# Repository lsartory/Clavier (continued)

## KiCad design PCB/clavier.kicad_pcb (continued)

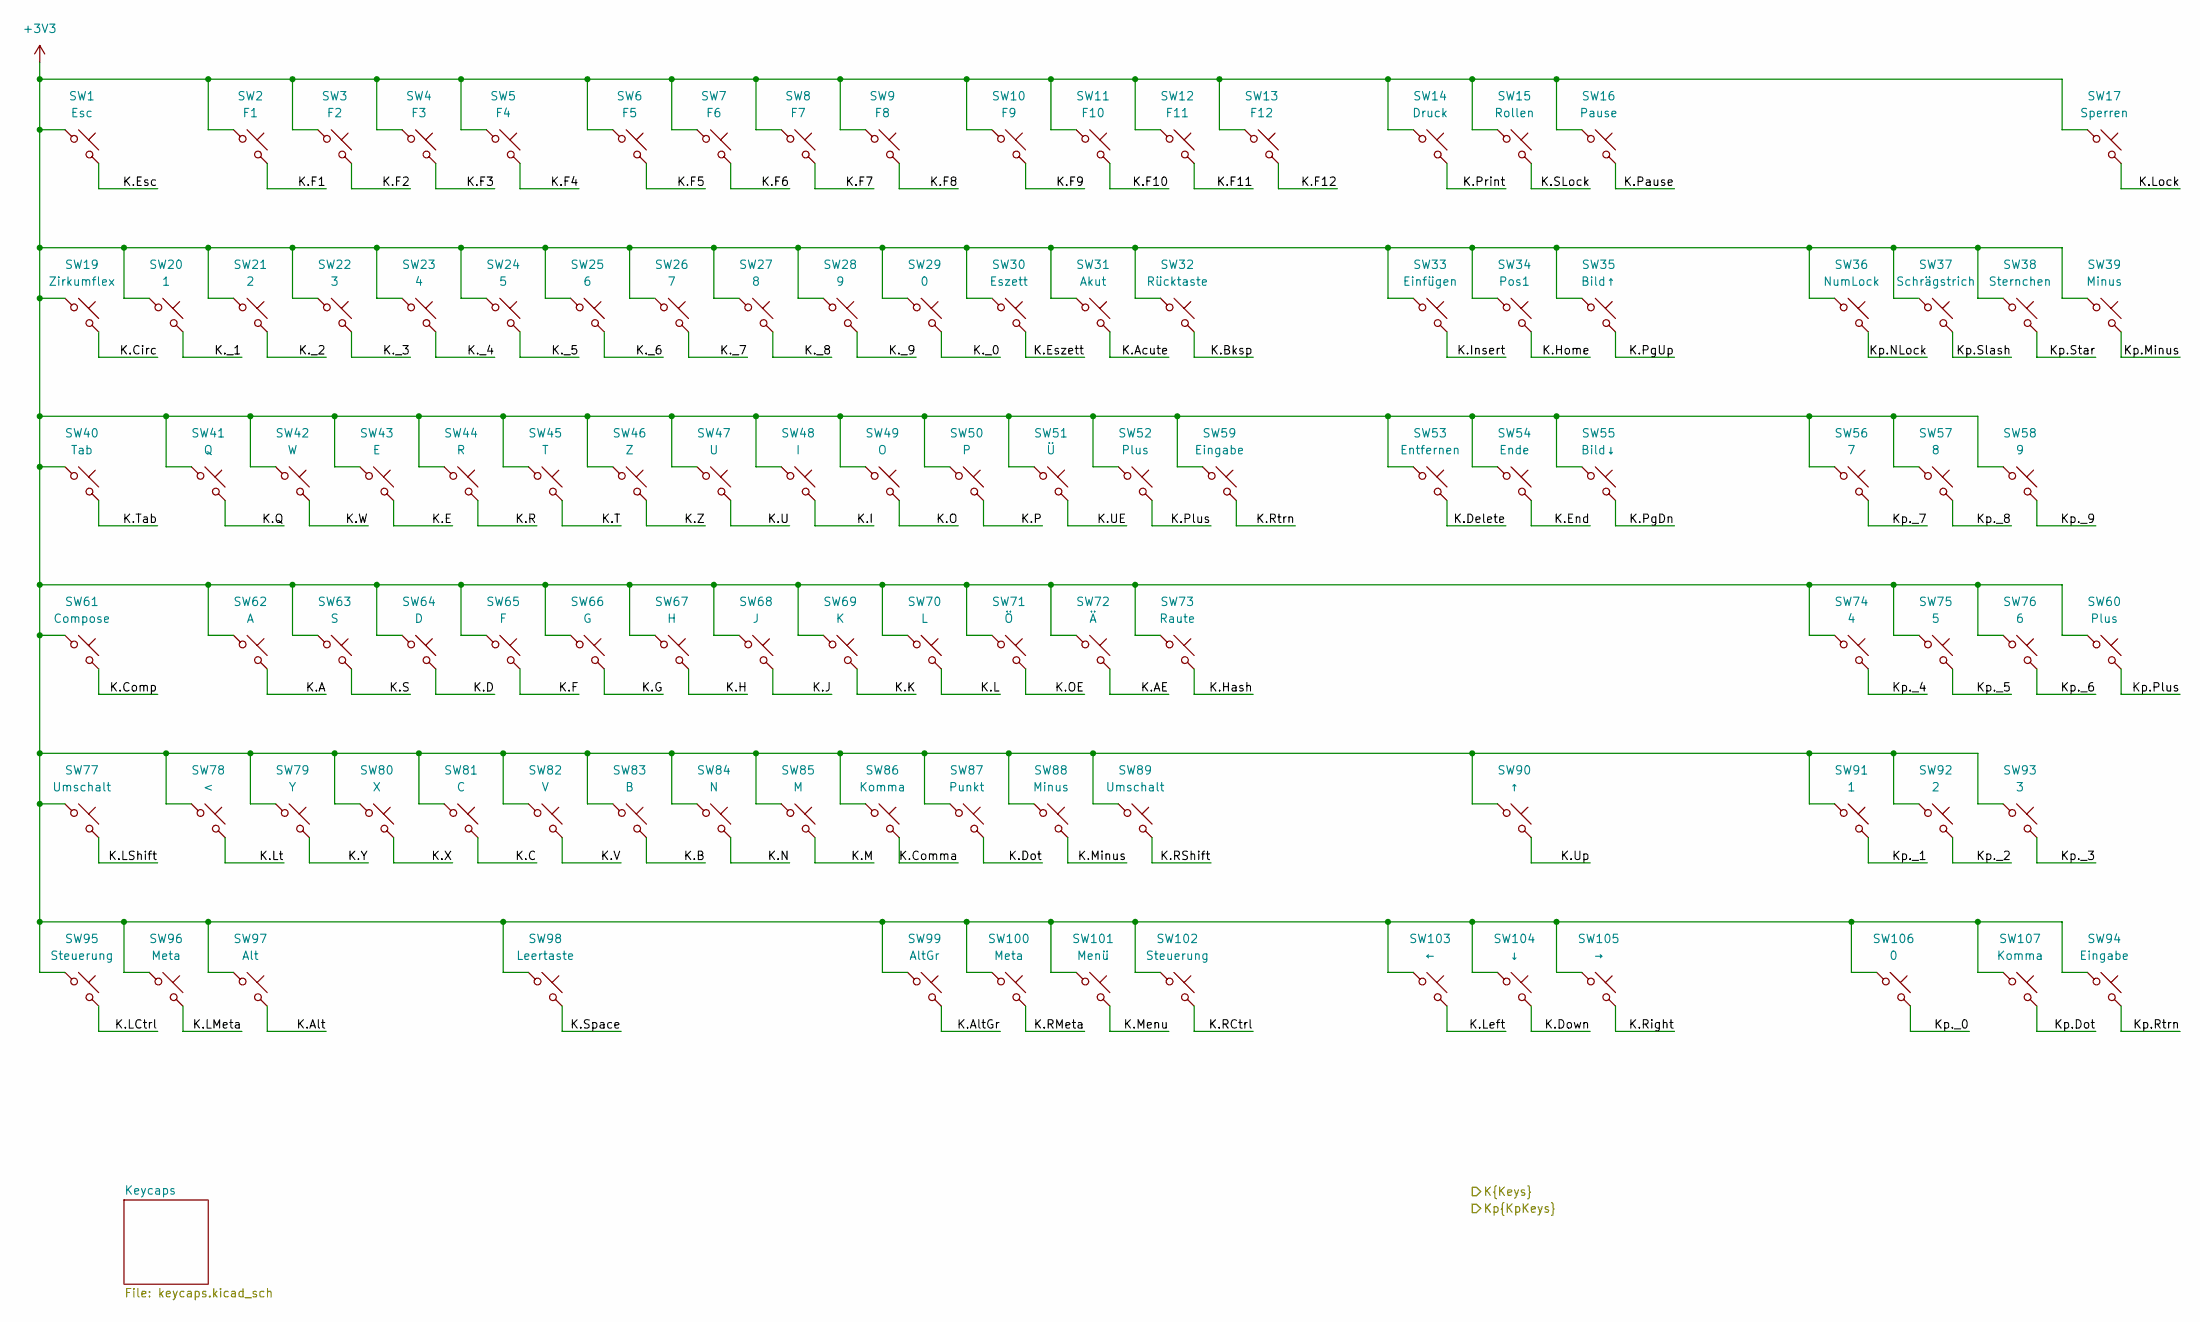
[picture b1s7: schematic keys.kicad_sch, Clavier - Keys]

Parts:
SW1, SW2, SW3, SW4, SW5, SW6, SW7, SW8, SW9, SW10, SW11, SW12, SW13, SW14, SW15, SW16, SW17, SW19, SW20, SW21, SW22, SW23, SW24, SW25, SW26, SW27, SW28, SW29, SW30, SW31, SW33, SW34, SW35, SW36, SW37, SW38, SW39, SW41, SW42, SW43, SW44, SW45, SW46, SW47, SW48, SW49, SW50, SW51, SW52, SW53, SW54, SW55, SW56, SW57, SW58, SW62, SW63, SW64, SW65, SW66, SW67, SW68, SW69, SW70, SW71, SW72, SW73, SW74, SW75, SW76, SW78, SW79, SW80, SW81, SW82, SW83, SW84, SW85, SW86, SW87, SW88, SW90, SW91, SW92, SW93, SW103, SW104, SW105, SW107: SW_Cherry_MX_1.00u_PCB
SW32, SW106: SW_Cherry_MX_2.00u_PCB
SW40: SW_Cherry_MX_1.50u_PCB
SW59: SW_Cherry_MX_ISOEnter_PCB
SW60, SW94: SW_Cherry_MX_2.00u_Vertical_PCB
SW61: SW_Cherry_MX_1.75u_PCB
SW77, SW95, SW96, SW97, SW99, SW100, SW101, SW102: SW_Cherry_MX_1.25u_PCB
SW89: SW_Cherry_MX_2.75u_PCB
SW98: SW_Cherry_MX_6.25u_PCB

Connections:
+3V3: SW1.1, SW2.1, SW3.1, SW4.1, SW5.1, SW6.1, SW7.1, SW8.1, SW9.1, SW10.1, SW11.1, SW12.1, SW13.1, SW14.1, SW15.1, SW16.1, SW17.1, SW19.1, SW20.1, SW21.1, SW22.1, SW23.1, SW24.1, SW25.1, SW26.1, SW27.1, SW28.1, SW29.1, SW30.1, SW31.1, SW32.1, SW33.1, SW34.1, SW35.1, SW36.1, SW37.1, SW38.1, SW39.1, SW40.1, SW41.1, SW42.1, SW43.1, SW44.1, SW45.1, SW46.1, SW47.1, SW48.1, SW49.1, SW50.1, SW51.1, SW52.1, SW53.1, SW54.1, SW55.1, SW56.1, SW57.1, SW58.1, SW59.1, SW60.1, SW61.1, SW62.1, SW63.1, SW64.1, SW65.1, SW66.1, SW67.1, SW68.1, SW69.1, SW70.1, SW71.1, SW72.1, SW73.1, SW74.1, SW75.1, SW76.1, SW77.1, SW78.1, SW79.1, SW80.1, SW81.1, SW82.1, SW83.1, SW84.1, SW85.1, SW86.1, SW87.1, SW88.1, SW89.1, SW90.1, SW91.1, SW92.1, SW93.1, SW94.1, SW95.1, SW96.1, SW97.1, SW98.1, SW99.1, SW100.1, SW101.1, SW102.1, SW103.1, SW104.1, SW105.1, SW106.1, SW107.1; also elsewhere on the board
/FPGA/K.A: SW62.2; also elsewhere on the board
/FPGA/K.AE: SW72.2; also elsewhere on the board
/FPGA/K.Acute: SW31.2; also elsewhere on the board
/FPGA/K.Alt: SW97.2; also elsewhere on the board
/FPGA/K.AltGr: SW99.2; also elsewhere on the board
/FPGA/K.B: SW83.2; also elsewhere on the board
/FPGA/K.Bksp: SW32.2; also elsewhere on the board
/FPGA/K.C: SW81.2; also elsewhere on the board
/FPGA/K.Circ: SW19.2; also elsewhere on the board
/FPGA/K.Comma: SW86.2; also elsewhere on the board
/FPGA/K.Comp: SW61.2; also elsewhere on the board
/FPGA/K.D: SW64.2; also elsewhere on the board
/FPGA/K.Delete: SW53.2; also elsewhere on the board
/FPGA/K.Dot: SW87.2; also elsewhere on the board
/FPGA/K.Down: SW104.2; also elsewhere on the board
/FPGA/K.E: SW43.2; also elsewhere on the board
/FPGA/K.End: SW54.2; also elsewhere on the board
/FPGA/K.Esc: SW1.2; also elsewhere on the board
/FPGA/K.Eszett: SW30.2; also elsewhere on the board
/FPGA/K.F: SW65.2; also elsewhere on the board
/FPGA/K.F1: SW2.2; also elsewhere on the board
/FPGA/K.F2: SW3.2; also elsewhere on the board
/FPGA/K.F3: SW4.2; also elsewhere on the board
/FPGA/K.F4: SW5.2; also elsewhere on the board
/FPGA/K.F5: SW6.2; also elsewhere on the board
/FPGA/K.F6: SW7.2; also elsewhere on the board
/FPGA/K.F7: SW8.2; also elsewhere on the board
/FPGA/K.F8: SW9.2; also elsewhere on the board
/FPGA/K.F9: SW10.2; also elsewhere on the board
/FPGA/K.F10: SW11.2; also elsewhere on the board
/FPGA/K.F11: SW12.2; also elsewhere on the board
/FPGA/K.F12: SW13.2; also elsewhere on the board
/FPGA/K.G: SW66.2; also elsewhere on the board
/FPGA/K.H: SW67.2; also elsewhere on the board
/FPGA/K.Hash: SW73.2; also elsewhere on the board
/FPGA/K.Home: SW34.2; also elsewhere on the board
/FPGA/K.I: SW48.2; also elsewhere on the board
/FPGA/K.Insert: SW33.2; also elsewhere on the board
/FPGA/K.J: SW68.2; also elsewhere on the board
/FPGA/K.K: SW69.2; also elsewhere on the board
/FPGA/K.L: SW70.2; also elsewhere on the board
/FPGA/K.LCtrl: SW95.2; also elsewhere on the board
/FPGA/K.LMeta: SW96.2; also elsewhere on the board
/FPGA/K.LShift: SW77.2; also elsewhere on the board
/FPGA/K.Left: SW103.2; also elsewhere on the board
/FPGA/K.Lock: SW17.2; also elsewhere on the board
/FPGA/K.Lt: SW78.2; also elsewhere on the board
/FPGA/K.M: SW85.2; also elsewhere on the board
/FPGA/K.Menu: SW101.2; also elsewhere on the board
/FPGA/K.Minus: SW88.2; also elsewhere on the board
/FPGA/K.N: SW84.2; also elsewhere on the board
/FPGA/K.O: SW49.2; also elsewhere on the board
/FPGA/K.OE: SW71.2; also elsewhere on the board
/FPGA/K.P: SW50.2; also elsewhere on the board
/FPGA/K.Pause: SW16.2; also elsewhere on the board
/FPGA/K.PgDn: SW55.2; also elsewhere on the board
/FPGA/K.PgUp: SW35.2; also elsewhere on the board
/FPGA/K.Plus: SW52.2; also elsewhere on the board
/FPGA/K.Print: SW14.2; also elsewhere on the board
/FPGA/K.Q: SW41.2; also elsewhere on the board
/FPGA/K.R: SW44.2; also elsewhere on the board
/FPGA/K.RCtrl: SW102.2; also elsewhere on the board
/FPGA/K.RMeta: SW100.2; also elsewhere on the board
/FPGA/K.RShift: SW89.2; also elsewhere on the board
/FPGA/K.Right: SW105.2; also elsewhere on the board
/FPGA/K.Rtrn: SW59.2; also elsewhere on the board
/FPGA/K.S: SW63.2; also elsewhere on the board
/FPGA/K.SLock: SW15.2; also elsewhere on the board
/FPGA/K.Space: SW98.2; also elsewhere on the board
/FPGA/K.T: SW45.2; also elsewhere on the board
/FPGA/K.Tab: SW40.2; also elsewhere on the board
/FPGA/K.U: SW47.2; also elsewhere on the board
/FPGA/K.UE: SW51.2; also elsewhere on the board
/FPGA/K.Up: SW90.2; also elsewhere on the board
/FPGA/K.V: SW82.2; also elsewhere on the board
/FPGA/K.W: SW42.2; also elsewhere on the board
/FPGA/K.X: SW80.2; also elsewhere on the board
/FPGA/K.Y: SW79.2; also elsewhere on the board
/FPGA/K.Z: SW46.2; also elsewhere on the board
/FPGA/K._0: SW29.2; also elsewhere on the board
/FPGA/K._1: SW20.2; also elsewhere on the board
/FPGA/K._2: SW21.2; also elsewhere on the board
/FPGA/K._3: SW22.2; also elsewhere on the board
/FPGA/K._4: SW23.2; also elsewhere on the board
/FPGA/K._5: SW24.2; also elsewhere on the board
/FPGA/K._6: SW25.2; also elsewhere on the board
/FPGA/K._7: SW26.2; also elsewhere on the board
/FPGA/K._8: SW27.2; also elsewhere on the board
/FPGA/K._9: SW28.2; also elsewhere on the board
/FPGA/Kp.Dot: SW107.2; also elsewhere on the board
/FPGA/Kp.Minus: SW39.2; also elsewhere on the board
/FPGA/Kp.NLock: SW36.2; also elsewhere on the board
/FPGA/Kp.Plus: SW60.2; also elsewhere on the board
/FPGA/Kp.Rtrn: SW94.2; also elsewhere on the board
/FPGA/Kp.Slash: SW37.2; also elsewhere on the board
/FPGA/Kp.Star: SW38.2; also elsewhere on the board
/FPGA/Kp._0: SW106.2; also elsewhere on the board
/FPGA/Kp._1: SW91.2; also elsewhere on the board
/FPGA/Kp._2: SW92.2; also elsewhere on the board
/FPGA/Kp._3: SW93.2; also elsewhere on the board
/FPGA/Kp._4: SW74.2; also elsewhere on the board
/FPGA/Kp._5: SW75.2; also elsewhere on the board
/FPGA/Kp._6: SW76.2; also elsewhere on the board
/FPGA/Kp._7: SW56.2; also elsewhere on the board
/FPGA/Kp._8: SW57.2; also elsewhere on the board
/FPGA/Kp._9: SW58.2; also elsewhere on the board

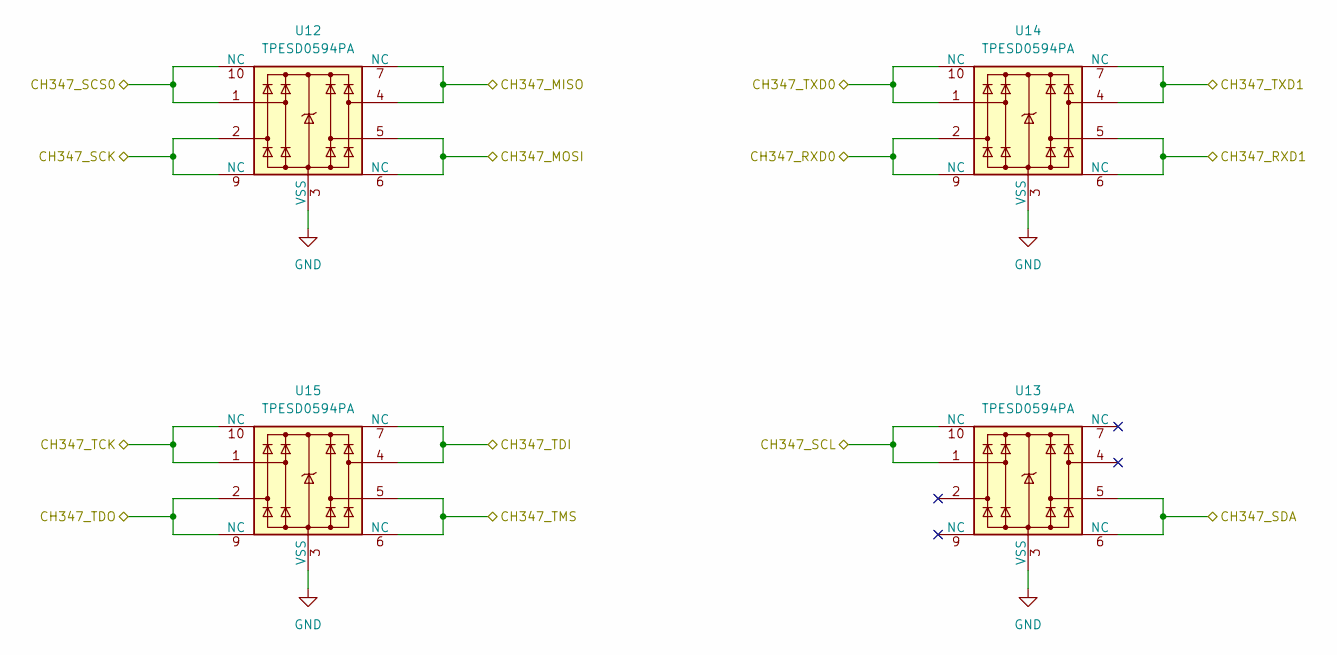
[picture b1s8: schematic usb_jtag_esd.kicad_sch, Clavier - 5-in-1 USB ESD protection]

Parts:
U12, U13, U14, U15: TPESD0594PA; Diodes_UDFN-10_1.0x2.5mm_P0.5mm; Part_number TPESD0594PA; LCSC C42436622

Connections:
/5-in-1 USB/CH347_MISO: U12.4, U12.7 (NC); also elsewhere on the board
/5-in-1 USB/CH347_MOSI: U12.5, U12.6 (NC); also elsewhere on the board
/5-in-1 USB/CH347_RXD0: U14.2, U14.9 (NC); also elsewhere on the board
/5-in-1 USB/CH347_RXD1: U14.5, U14.6 (NC); also elsewhere on the board
/5-in-1 USB/CH347_SCK: U12.2, U12.9 (NC); also elsewhere on the board
/5-in-1 USB/CH347_SCL: U13.1, U13.10 (NC); also elsewhere on the board
/5-in-1 USB/CH347_SCS0: U12.1, U12.10 (NC); also elsewhere on the board
/5-in-1 USB/CH347_SDA: U13.5, U13.6 (NC); also elsewhere on the board
/5-in-1 USB/CH347_TCK: U15.1, U15.10 (NC); also elsewhere on the board
/5-in-1 USB/CH347_TDI: U15.4, U15.7 (NC); also elsewhere on the board
/5-in-1 USB/CH347_TDO: U15.2, U15.9 (NC); also elsewhere on the board
/5-in-1 USB/CH347_TMS: U15.5, U15.6 (NC); also elsewhere on the board
/5-in-1 USB/CH347_TXD0: U14.1, U14.10 (NC); also elsewhere on the board
/5-in-1 USB/CH347_TXD1: U14.4, U14.7 (NC); also elsewhere on the board
GND: U12.3 (VSS), U12.8 (VSS), U13.3 (VSS), U13.8 (VSS), U14.3 (VSS), U14.8 (VSS), U15.3 (VSS), U15.8 (VSS); also elsewhere on the board

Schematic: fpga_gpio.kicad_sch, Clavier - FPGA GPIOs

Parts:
J5, J6: Pin header, 2x4; PinHeader_2x04_P2.54mm_Vertical; Part_number ZX-PZ2.54-2-4PZZ; LCSC C7501275
U2, U3, U9, U10: TPESD0594PA; Diodes_UDFN-10_1.0x2.5mm_P0.5mm; Part_number TPESD0594PA; LCSC C42436622

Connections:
/FPGA/FPGA_GPIO0: J5.1, U3.2, U3.9 (NC); also elsewhere on the board
/FPGA/FPGA_GPIO1: J5.3, U3.1, U3.10 (NC); also elsewhere on the board
/FPGA/FPGA_GPIO2: J5.5, U10.1, U10.10 (NC); also elsewhere on the board
/FPGA/FPGA_GPIO3: J5.7, U10.2, U10.9 (NC); also elsewhere on the board
/FPGA/FPGA_GPIO4: J5.2, U3.4, U3.7 (NC); also elsewhere on the board
/FPGA/FPGA_GPIO5: J5.4, U3.5, U3.6 (NC); also elsewhere on the board
/FPGA/FPGA_GPIO6: J5.6, U10.5, U10.6 (NC); also elsewhere on the board
/FPGA/FPGA_GPIO7: J5.8, U10.4, U10.7 (NC); also elsewhere on the board
/FPGA/FPGA_GPIO8: J6.1, U2.2, U2.9 (NC); also elsewhere on the board
/FPGA/FPGA_GPIO9: J6.3, U2.1, U2.10 (NC); also elsewhere on the board
/FPGA/FPGA_GPIO10: J6.5, U9.1, U9.10 (NC); also elsewhere on the board
/FPGA/FPGA_GPIO11: J6.7, U9.2, U9.9 (NC); also elsewhere on the board
/FPGA/FPGA_GPIO12: J6.2, U2.4, U2.7 (NC); also elsewhere on the board
/FPGA/FPGA_GPIO13: J6.4, U2.5, U2.6 (NC); also elsewhere on the board
/FPGA/FPGA_GPIO14: J6.6, U9.5, U9.6 (NC); also elsewhere on the board
/FPGA/FPGA_GPIO15: J6.8, U9.4, U9.7 (NC); also elsewhere on the board
GND: U2.3 (VSS), U2.8 (VSS), U3.3 (VSS), U3.8 (VSS), U9.3 (VSS), U9.8 (VSS), U10.3 (VSS), U10.8 (VSS); also elsewhere on the board

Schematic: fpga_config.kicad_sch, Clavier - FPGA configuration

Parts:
C30: 100nF; C_0402_1005Metric_Pad0.74x0.62mm_HandSolder; Voltage 50V; Part_number GRM155R71H104KE14D; LCSC C77020
C31, C40: 1µF; C_0402_1005Metric_Pad0.74x0.62mm_HandSolder; Voltage 50V; Part_number GRM155R61H105KE05D; LCSC C1518208
J8: Pin header, 1x4; PinHeader_1x04_P2.54mm_Horizontal; Part_number ZX-PZ2.54-1-4PWZ; LCSC C7501292
R9: 1kΩ; R_0402_1005Metric_Pad0.72x0.64mm_HandSolder; Part_number RE0402DRE071KL; LCSC C851917
R10, R11, R12, R32: 10kΩ; R_0402_1005Metric_Pad0.72x0.64mm_HandSolder; Part_number RE0402DRE0710KL; LCSC C851874
U5: TPESD0594PA; Diodes_UDFN-10_1.0x2.5mm_P0.5mm; Part_number TPESD0594PA; LCSC C42436622
U18: LFE5U-25F-6BG256C; BGA-256_14.0x14.0mm_Layout16x16_P0.8mm_Ball0.45mm_Pad0.32mm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; Part_number LFE5U-25F-6BG256C; LCSC C1521614
U19: W25Q128JVSIQ; SOIC-8_5.3x5.3mm_P1.27mm; Part_number W25Q128JVSIQ; LCSC C113767

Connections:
+3V3: C30.1, C31.1, C40.1, R10.1, R11.1, R12.1, R32.1, U18.L6 (VCCIO8), U18.P10 (CFG_1), U19.8 (VCC); also elsewhere on the board
/FPGA/FPGA config/FPGA_TCK: J8.1, R9.1, U5.1, U5.10 (NC), U18.T10 (TCK)
/FPGA/FPGA config/FPGA_TDI: J8.3, R11.2, U5.4, U5.7 (NC), U18.R11 (TDI)
/FPGA/FPGA config/FPGA_TDO: J8.2, R10.2, U5.2, U5.9 (NC), U18.M10 (TDO)
/FPGA/FPGA config/FPGA_TMS: J8.4, R12.2, U5.5, U5.6 (NC), U18.T11 (TMS)
/FPGA/FPGA config/FPGA_~Reset: U18.R8 (PB13A), U18.R9 (~PROGRAM)
/FPGA/FPGA config/Flash_CLK: U18.N9 (CCLK), U19.6 (CLK)
/FPGA/FPGA config/Flash_IO0: U18.T8 (PB11B), U19.5 (DI/IO_{0})
/FPGA/FPGA config/Flash_IO1: U18.T7 (PB11A), U19.2 (DO/IO_{1})
/FPGA/FPGA config/Flash_IO2: U18.M7 (PB9B), U19.3 (~WP/IO_{2})
/FPGA/FPGA config/Flash_IO3: U18.N7 (PB9A), U19.7 (~HOLD/~RESET/IO_{3})
/FPGA/FPGA config/Flash_~CS: R32.2, U18.N8 (PB15A), U19.1 (~CS)
GND: C30.2, C31.2, C40.2, R9.2, U5.3 (VSS), U5.8 (VSS), U18.N10 (CFG_0), U18.R10 (CFG_2), U19.4 (GND); also elsewhere on the board

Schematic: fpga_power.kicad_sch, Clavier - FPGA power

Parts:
C27, C28, C38: 1µF; C_0402_1005Metric_Pad0.74x0.62mm_HandSolder; Voltage 50V; Part_number GRM155R61H105KE05D; LCSC C1518208
C29, C39: 100nF; C_0402_1005Metric_Pad0.74x0.62mm_HandSolder; Voltage 50V; Part_number GRM155R71H104KE14D; LCSC C77020
U18: LFE5U-25F-6BG256C; BGA-256_14.0x14.0mm_Layout16x16_P0.8mm_Ball0.45mm_Pad0.32mm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; Part_number LFE5U-25F-6BG256C; LCSC C1521614

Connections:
+1V1: C27.1, C28.1, C29.1, U18.G6 (VCC), U18.G7 (VCC), U18.G9 (VCC), U18.L8 (VCC), U18.L9 (VCC), U18.L10 (VCC); also elsewhere on the board
+2V5: C38.1, C39.1, U18.G11 (VCCAUX), U18.L7 (VCCAUX); also elsewhere on the board
GND: C27.2, C28.2, C29.2, C38.2, C39.2, U18.A1 (GND), U18.A16 (GND), U18.D2 (GND), U18.D15 (GND), U18.F8 (GND), U18.F9 (GND), U18.G8 (GND), U18.G10 (GND), U18.H1 (GND), U18.H8 (GND), U18.H9 (GND), U18.H10 (GND), U18.H16 (GND), U18.J8 (GND), U18.J9 (GND), U18.J10 (GND), U18.K6 (GND), U18.K7 (GND), U18.K8 (GND), U18.K9 (GND), U18.K10 (GND), U18.N2 (GND), U18.N15 (GND), U18.T1 (GND), U18.T5 (GND), U18.T12 (GND), U18.T16 (GND); also elsewhere on the board

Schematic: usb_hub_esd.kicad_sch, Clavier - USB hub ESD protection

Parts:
U1, U4, U11: TPESD0594PA; Diodes_UDFN-10_1.0x2.5mm_P0.5mm; Part_number TPESD0594PA; LCSC C42436622

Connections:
/USB hub/D2+: U4.1, U4.10 (NC); also elsewhere on the board
/USB hub/D2-: U4.2, U4.9 (NC); also elsewhere on the board
/USB hub/D4+: U11.1, U11.10 (NC); also elsewhere on the board
/USB hub/D4-: U11.2, U11.9 (NC); also elsewhere on the board
/USB hub/D+: U1.1, U1.10 (NC); also elsewhere on the board
/USB hub/D-: U1.2, U1.9 (NC); also elsewhere on the board
GND: U1.3 (VSS), U1.8 (VSS), U4.3 (VSS), U4.8 (VSS), U11.3 (VSS), U11.8 (VSS); also elsewhere on the board

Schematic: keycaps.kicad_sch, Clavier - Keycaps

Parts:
KC1, KC2, KC3, KC4, KC5, KC6, KC7, KC8, KC9, KC10, KC11, KC12, KC13, KC14, KC15, KC16, KC18, KC23, KC26, KC32, KC33, KC34, KC35, KC36, KC37, KC38: KC_Cherry_MX_R1_1.00u_Black
KC17: KC_Cherry_MX_R1_1.00u_Red
KC19, KC20, KC21, KC22, KC24, KC25, KC27, KC28, KC29, KC30: KC_Cherry_MX_R1_1.00u_White
KC31: KC_Cherry_MX_R1_2.00u_Black
KC39: KC_Cherry_MX_R2_1.50u_Black
KC40, KC41, KC42, KC43, KC44, KC45, KC46, KC47, KC48, KC49, KC50, KC51, KC55, KC56, KC57: KC_Cherry_MX_R2_1.00u_White
KC52, KC53, KC54: KC_Cherry_MX_R2_1.00u_Black
KC58: KC_Cherry_MX_R2-R3_ISO_Enter_Black
KC59: KC_Cherry_MX_R2-R3_1.00u_Black
KC60: KC_Cherry_MX_R3_1.75u_Black
KC61, KC62, KC63, KC65, KC66, KC68, KC69, KC70, KC71, KC72, KC73, KC74, KC75: KC_Cherry_MX_R3_1.00u_White
KC64, KC67: KC_Cherry_MX_R3_1.00u_Barred_Black
KC76, KC94, KC95, KC96, KC97, KC98, KC99, KC100: KC_Cherry_MX_R4_1.25u_Black
KC77, KC78, KC79, KC80, KC81, KC82, KC83, KC84, KC85, KC86, KC87, KC90, KC91, KC92, KC105: KC_Cherry_MX_R4_1.00u_White
KC88: KC_Cherry_MX_R4_2.75u_Black
KC89, KC101, KC102, KC103: KC_Cherry_MX_R4_1.00u_Black
KC93: KC_Cherry_MX_R4-R4_1.00u_Black
KC104: KC_Cherry_MX_R4_2.00u_White
KC106: KC_Cherry_MX_R4_6.25u_Black
ST1, ST2, ST3, ST4, ST5, ST7: Stabilizer_2.00u
ST6: Stabilizer_6.25u

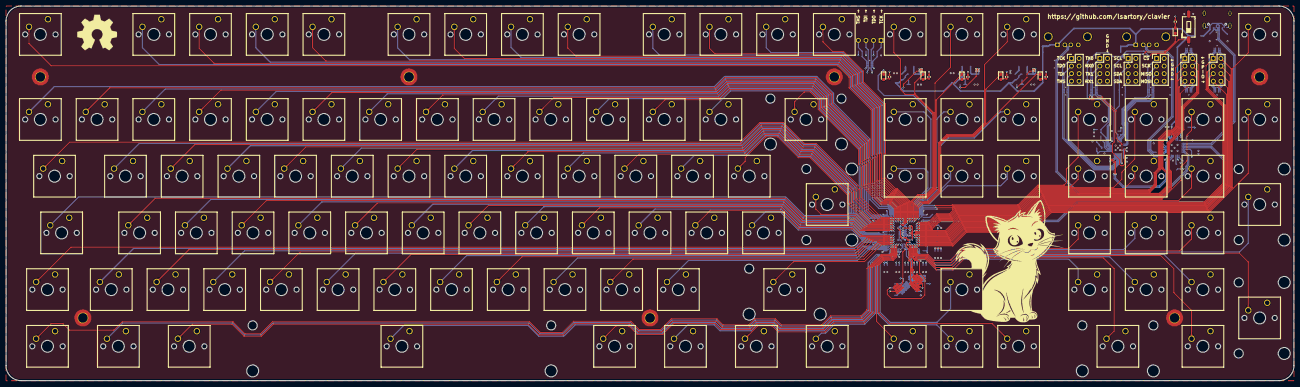
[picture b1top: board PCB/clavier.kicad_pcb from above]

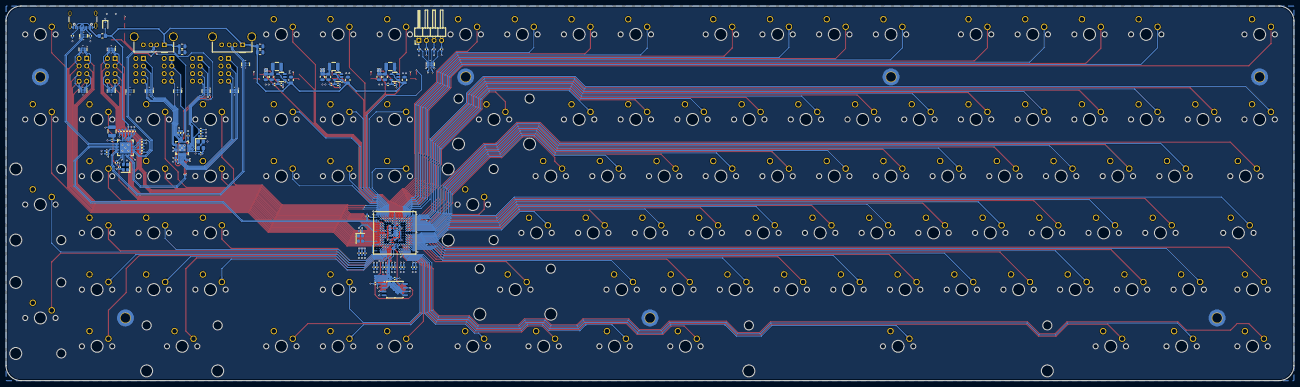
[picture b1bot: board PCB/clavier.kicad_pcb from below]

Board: 4 copper layers, 431.5 x 125.5 mm, 344 parts (98 on the bottom side), 199 nets.

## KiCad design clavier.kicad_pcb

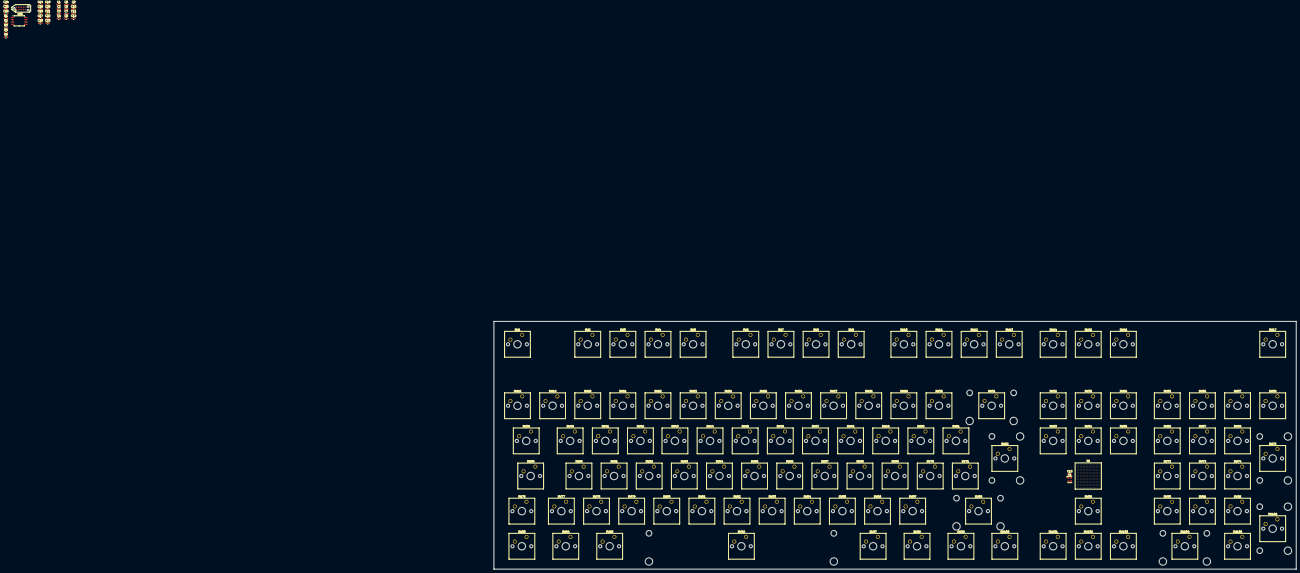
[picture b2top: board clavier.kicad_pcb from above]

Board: 4 copper layers, 434.0 x 134.0 mm, 141 parts (0 on the bottom side), 29 nets, no tracks yet.

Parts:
C1, C3, C5, C7, C9, C11, C13, C14, C15, C17, C19, C20, C22, C25, C26: 1µF; C_0603_1608Metric
C2, C4, C6, C8, C10, C12, C16, C18, C21, C23, C24: 100nF; C_0603_1608Metric
J1: TC2050; Tag-Connect_TC2050-IDC-NL_2x05_P1.27mm_Vertical_with_bottom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
R1, R2, R3, R4: 10k; R_0603_1608Metric
R5: 1k; R_0603_1608Metric
SW1: Esc; SW_Cherry_MX_1.00u_PCB
SW2: F1; SW_Cherry_MX_1.00u_PCB
SW3: F2; SW_Cherry_MX_1.00u_PCB
SW4: F3; SW_Cherry_MX_1.00u_PCB
SW5: F4; SW_Cherry_MX_1.00u_PCB
SW6: F5; SW_Cherry_MX_1.00u_PCB
SW7: F6; SW_Cherry_MX_1.00u_PCB
SW8: F7; SW_Cherry_MX_1.00u_PCB
SW9: F8; SW_Cherry_MX_1.00u_PCB
SW10: F9; SW_Cherry_MX_1.00u_PCB
SW11: F10; SW_Cherry_MX_1.00u_PCB
SW12: F11; SW_Cherry_MX_1.00u_PCB
SW13: F12; SW_Cherry_MX_1.00u_PCB
SW14: Druck; SW_Cherry_MX_1.00u_PCB
SW15: Rollen; SW_Cherry_MX_1.00u_PCB
SW16: Pause; SW_Cherry_MX_1.00u_PCB
SW17: Sperren; SW_Cherry_MX_1.00u_PCB
SW18: Zirkumflex; SW_Cherry_MX_1.00u_PCB
SW19, SW90: 1; SW_Cherry_MX_1.00u_PCB
SW20, SW91: 2; SW_Cherry_MX_1.00u_PCB
SW21, SW92: 3; SW_Cherry_MX_1.00u_PCB
SW22, SW72: 4; SW_Cherry_MX_1.00u_PCB
SW23, SW73: 5; SW_Cherry_MX_1.00u_PCB
SW24, SW74: 6; SW_Cherry_MX_1.00u_PCB
SW25, SW56: 7; SW_Cherry_MX_1.00u_PCB
SW26, SW57: 8; SW_Cherry_MX_1.00u_PCB
SW27, SW58: 9; SW_Cherry_MX_1.00u_PCB
SW28: 0; SW_Cherry_MX_1.00u_PCB
SW29: Eszett; SW_Cherry_MX_1.00u_PCB
SW30: Akut; SW_Cherry_MX_1.00u_PCB
SW31: Rücktaste; SW_Cherry_MX_2.00u_PCB
SW32: Einfügen; SW_Cherry_MX_1.00u_PCB
SW33: Pos1; SW_Cherry_MX_1.00u_PCB
SW34: Bild↑; SW_Cherry_MX_1.00u_PCB
SW35: NumLock; SW_Cherry_MX_1.00u_PCB
SW36: Schrägstrich; SW_Cherry_MX_1.00u_PCB
SW37: Sternchen; SW_Cherry_MX_1.00u_PCB
SW38, SW87: Minus; SW_Cherry_MX_1.00u_PCB
SW39: Tab; SW_Cherry_MX_1.50u_PCB
SW40: Q; SW_Cherry_MX_1.00u_PCB
SW41: W; SW_Cherry_MX_1.00u_PCB
SW42: E; SW_Cherry_MX_1.00u_PCB
SW43: R; SW_Cherry_MX_1.00u_PCB
SW44: T; SW_Cherry_MX_1.00u_PCB
SW45: Z; SW_Cherry_MX_1.00u_PCB
SW46: U; SW_Cherry_MX_1.00u_PCB
SW47: I; SW_Cherry_MX_1.00u_PCB
SW48: O; SW_Cherry_MX_1.00u_PCB
SW49: P; SW_Cherry_MX_1.00u_PCB
SW50: Ü; SW_Cherry_MX_1.00u_PCB
SW51: Plus; SW_Cherry_MX_1.00u_PCB
SW52: Eingabe; SW_Cherry_MX_ISOEnter_PCB
SW53: Entfernen; SW_Cherry_MX_1.00u_PCB
SW54: Ende; SW_Cherry_MX_1.00u_PCB
SW55: Bild↓; SW_Cherry_MX_1.00u_PCB
SW59: Compose; SW_Cherry_MX_1.75u_PCB
SW60: A; SW_Cherry_MX_1.00u_PCB
SW61: S; SW_Cherry_MX_1.00u_PCB
SW62: D; SW_Cherry_MX_1.00u_PCB
SW63: F; SW_Cherry_MX_1.00u_PCB
SW64: G; SW_Cherry_MX_1.00u_PCB
SW65: H; SW_Cherry_MX_1.00u_PCB
SW66: J; SW_Cherry_MX_1.00u_PCB
SW67: K; SW_Cherry_MX_1.00u_PCB
SW68: L; SW_Cherry_MX_1.00u_PCB
SW69: Ö; SW_Cherry_MX_1.00u_PCB
SW70: Ä; SW_Cherry_MX_1.00u_PCB
SW71: Raute; SW_Cherry_MX_1.00u_PCB
SW75: Plus; SW_Cherry_MX_2.00u_Vertical_PCB
SW76: Umschalt; SW_Cherry_MX_1.25u_PCB
SW77: <; SW_Cherry_MX_1.00u_PCB
SW78: Y; SW_Cherry_MX_1.00u_PCB
SW79: X; SW_Cherry_MX_1.00u_PCB
SW80: C; SW_Cherry_MX_1.00u_PCB
SW81: V; SW_Cherry_MX_1.00u_PCB
SW82: B; SW_Cherry_MX_1.00u_PCB
SW83: N; SW_Cherry_MX_1.00u_PCB
SW84: M; SW_Cherry_MX_1.00u_PCB
SW85, SW105: Komma; SW_Cherry_MX_1.00u_PCB
SW86: Punkt; SW_Cherry_MX_1.00u_PCB
SW88: Umschalt; SW_Cherry_MX_2.75u_PCB
SW89: ↑; SW_Cherry_MX_1.00u_PCB
SW93, SW100: Steuerung; SW_Cherry_MX_1.25u_PCB
SW94, SW98: Meta; SW_Cherry_MX_1.25u_PCB
SW95: Alt; SW_Cherry_MX_1.25u_PCB
SW96: Leertaste; SW_Cherry_MX_6.25u_PCB
SW97: AltGr; SW_Cherry_MX_1.25u_PCB
SW99: Menü; SW_Cherry_MX_1.25u_PCB
SW101: ←; SW_Cherry_MX_1.00u_PCB
SW102: ↓; SW_Cherry_MX_1.00u_PCB
SW103: →; SW_Cherry_MX_1.00u_PCB
SW104: 0; SW_Cherry_MX_2.00u_PCB
SW106: Eingabe; SW_Cherry_MX_2.00u_Vertical_PCB
U1: LFE5U-25F-6BG256x; BGA-256_14.0x14.0mm_Layout16x16_P0.8mm_Ball0.45mm_Pad0.32mm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
U2: W25Q128JVS; SOIC-8_5.3x5.3mm_P1.27mm
Y1: KC2520Z; Oscillator_SMD_Kyocera_KC2520Z-4Pin_2.5x2.0mm

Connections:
+1V1: C14.1, C15.1, C16.1, C19.1, C20.1, C21.1, U1.G6 (VCC), U1.G7 (VCC), U1.G9 (VCC), U1.L8 (VCC), U1.L9 (VCC), U1.L10 (VCC)
+2V5: C17.1, C18.1, C22.1, C23.1, U1.G11 (VCCAUX), U1.L7 (VCCAUX)
+3V3: C1.1, C2.1, C3.1, C4.1, C5.1, C6.1, C7.1, C8.1, C9.1, C10.1, C11.1, C12.1, C13.1, C24.1, C25.1, C26.1, J1.1, R1.1, R2.1, R3.1, R4.1, SW1.1, SW2.1, SW3.1, SW4.1, SW5.1, SW6.1, SW7.1, SW8.1, SW9.1, SW10.1, SW11.1, SW12.1, SW13.1, SW14.1, SW15.1, SW16.1, SW17.1, SW18.1, SW19.1, SW20.1, SW21.1, SW22.1, SW23.1, SW24.1, SW25.1, SW26.1, SW27.1, SW28.1, SW29.1, SW30.1, SW31.1, SW32.1, SW33.1, SW34.1, SW35.1, SW36.1, SW37.1, SW38.1, SW39.1, SW40.1, SW41.1, SW42.1, SW43.1, SW44.1, SW45.1, SW46.1, SW47.1, SW48.1, SW49.1, SW50.1, SW51.1, SW52.1, SW53.1, SW54.1, SW55.1, SW56.1, SW57.1, SW58.1, SW59.1, SW60.1, SW61.1, SW62.1, SW63.1, SW64.1, SW65.1, SW66.1, SW67.1, SW68.1, SW69.1, SW70.1, SW71.1, SW72.1, SW73.1, SW74.1, SW75.1, SW76.1, SW77.1, SW78.1, SW79.1, SW80.1, SW81.1, SW82.1, SW83.1, SW84.1, SW85.1, SW86.1, SW87.1, SW88.1, SW89.1, SW90.1, SW91.1, SW92.1, SW93.1, SW94.1, SW95.1, SW96.1, SW97.1, SW98.1, SW99.1, SW100.1, SW101.1, SW102.1, SW103.1, SW104.1, SW105.1, SW106.1, U1.F6 (VCCIO0), U1.F7 (VCCIO0), U1.F10 (VCCIO1), U1.F11 (VCCIO1), U1.H6 (VCCIO7), U1.H7 (VCCIO7), U1.H11 (VCCIO2), U1.J6 (VCCIO6), U1.J7 (VCCIO6), U1.J11 (VCCIO2), U1.K11 (VCCIO3), U1.L6 (VCCIO8), U1.L11 (VCCIO3), U1.P10 (CFG_1), U2.8 (VCC), Y1.4 (VCC)
/FPGA/CLK_48MHz: U1.M1 (PCLKT6_0), Y1.3 (CLK)
/FPGA/FPGA config/FPGA_TCK: J1.4, R5.1, U1.T10 (TCK)
/FPGA/FPGA config/FPGA_TDI: J1.8, R3.2, U1.R11 (TDI)
/FPGA/FPGA config/FPGA_TDO: J1.6, R2.2, U1.M10 (TDO)
/FPGA/FPGA config/FPGA_TMS: J1.2, R4.2, U1.T11 (TMS)
/FPGA/FPGA config/FPGA_~Reset: U1.R8 (PB13A), U1.R9 (~PROGRAM)
/FPGA/FPGA config/Flash_CLK: U1.N9 (CCLK), U2.6 (CLK)
/FPGA/FPGA config/Flash_IO0: U1.T8 (PB11B), U2.5 (DI/IO_{0})
/FPGA/FPGA config/Flash_IO1: U1.T7 (PB11A), U2.2 (DO/IO_{1})
/FPGA/FPGA config/Flash_IO2: U1.M7 (PB9B), U2.3 (~WP/IO_{2})
/FPGA/FPGA config/Flash_IO3: U1.N7 (PB9A), U2.7 (~HOLD/~RESET/IO_{3})
/FPGA/FPGA config/Flash_~CS: R1.2, U1.N8 (PB15A), U2.1 (~CS)
/FPGA/K.Esc: SW1.2, U1.A2 (PT4A)
/FPGA/K.F1: SW2.2, U1.A3 (PT6A)
/FPGA/K.F2: SW3.2, U1.A4 (PT6B)
/FPGA/K.F3: SW4.2, U1.E4 (PT9A)
/FPGA/K.F4: SW5.2, U1.D4 (PT9B)
/FPGA/K.F5: SW6.2, U1.B4 (PT11B)
/FPGA/K.F6: SW7.2, U1.E5 (PT13A)
/FPGA/K.F7: SW8.2, U1.D5 (PT13B)
/FPGA/K.F8: SW9.2, U1.C5 (PT15A)
/FPGA/K.F9: SW10.2, U1.A5 (PT18A)
/FPGA/K.F10: SW11.2, U1.A6 (PT18B)
/FPGA/K.F11: SW12.2, U1.E6 (PT20A)
/FPGA/K.F12: SW13.2, U1.D6 (PT20B)
GND: C1.2, C2.2, C3.2, C4.2, C5.2, C6.2, C7.2, C8.2, C9.2, C10.2, C11.2, C12.2, C13.2, C14.2, C15.2, C16.2, C17.2, C18.2, C19.2, C20.2, C21.2, C22.2, C23.2, C24.2, C25.2, C26.2, J1.3, R5.2, U1.A1 (GND), U1.A16 (GND), U1.D2 (GND), U1.D15 (GND), U1.F8 (GND), U1.F9 (GND), U1.G8 (GND), U1.G10 (GND), U1.H1 (GND), U1.H8 (GND), U1.H9 (GND), U1.H10 (GND), U1.H16 (GND), U1.J8 (GND), U1.J9 (GND), U1.J10 (GND), U1.K6 (GND), U1.K7 (GND), U1.K8 (GND), U1.K9 (GND), U1.K10 (GND), U1.N2 (GND), U1.N10 (CFG_0), U1.N15 (GND), U1.R10 (CFG_2), U1.T1 (GND), U1.T5 (GND), U1.T12 (GND), U1.T16 (GND), U2.4 (GND), Y1.2 (GND)

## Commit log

2025-05-24 Add all keys
2025-05-24 Initial commit of the PCB
2025-05-24 Move the PCB files to a subfolder
2025-05-25 Add more TODOs
2025-05-26 Add power supplies
2025-05-29 Add a USB hub
2025-05-29 Add the USB to JTAG bridge
2025-05-31 Improve the CH347F schematics and added 3D models
2025-06-01 Add LICENSE and minor improvements
    - Filled the title blocks
    - Connected the LEDs to the FPGA
    - Changed the FPGA programming header
    - Added USB fuse and capacitors
2025-06-01 Add the first row of keycaps
2025-06-01 Make the red key less flashy
2025-06-02 Add more keycaps
2025-06-08 Add all missing keycaps
2025-06-08 Add stabilizers
2025-06-08 Place and route peripheral components
2025-06-09 Fan-out the FPGA
2025-06-14 Improve the routing
2025-06-15 Route all critical signals
2025-06-18 Initial commit of the FPGA code
2025-06-18 Add a main LICENSE file
2025-06-18 Initial commit of the USB_Device file
2025-06-18 Implement a basic USB receiver
2025-06-19 Implement the bit stuffing function on the receiver side
2025-06-19 Improve the state machine
2025-06-19 Split the USB PHY into a separate file
2025-06-19 Decode token packets
2025-06-19 Reduce the USB clock speed to 48 MHz
2025-06-19 Decode handshake packets
2025-06-19 Change the line sampling algorithm
2025-06-19 Decode start-of-frame packets
2025-06-19 Fix the timers for the lower clock speed
2025-06-19 Validate data packets
2025-06-20 Add a transmitter to the USB PHY
2025-06-20 Acknowledge incoming data packets
2025-06-21 Add ESD protection
2025-06-21 Improve the ESD protection
2025-06-21 Complete the PCB routing
2025-06-22 Fix DRC errors and warnings
2025-06-22 Update the board information
2025-06-22 Crop the cat image to prevent covering pads
2025-06-22 Improve the receiver process
2025-06-22 Refactor the PHY to better match the USB specifications
2025-06-23 Add EndPoint0 stub and descriptors definitions
2025-06-23 Complete the USB descriptor tree
2025-06-24 Send descriptors (not working yet)
2025-06-25 Add a simple UART to debug the USB communication
    Only the transmitter half is currently implemented
2025-06-25 Implement endpoint 0 further
    And fix TX bit stuffing
2025-06-26 Reimplement endpoint 0 using a FSM
2025-06-27 Add support for class descriptors
2025-06-27 Disable reponses to unknown endpoint 0 requests
2025-06-27 Move the USB-related files into a subfolder
2025-06-28 Send USB HID descriptors
2025-06-29 Send USB HID reports
2025-07-29 Display the key state using the LEDs
    The input internal pull-down resistor seems not to be working
2025-07-30 Add pull-down resistors to the keys inputs
2025-07-30 Add I/O locations
2025-08-10 Visualize the keypresses with LEDs
    For debugging only
2025-08-11 First draft of the housing
2025-08-12 Add supports to the housing
2025-08-12 Fix the mounting holes documentation
2025-08-13 Add support ribs
2025-08-14 Add openings for USB and JTAG
2025-08-15 Add stabilizer openings
2025-08-19 Remake the housing using FreeCAD
2025-08-19 Add more rounding to the supports
2025-08-19 Add a technical drawing
2025-08-20 Improve the technical drawing
2025-08-23 Map USB codes to the physical keys
2025-08-23 Add a basic README file
2025-08-24 Improve the README
2025-08-24 Fix the "context menu" key
2025-09-03 Implement an LED startup animation
2025-09-04 Implement key debouncing
    Fixes issue #2
2025-09-05 Add a couple helper functions to improve readability
2025-09-05 Improve the debouncing filter
    To increase immunity against noise / crosstalk
2025-09-05 Disable USB debugging by default
2025-09-07 Start redesigning the housing in a more ergonomic way
2025-09-09 Remap KEY_F20 to KEY_COFFEE
2025-09-09 Fix bit stuffing at the end of a transmission
    Fixes issues #5
2025-09-09 Complete the second version of the housing
2025-09-10 Add ribs to the housing
2025-09-11 Fix USB string max length and use the git hash as the device serial number
2025-09-11 Reset the FPGA when long-pressing the coffee key
2025-09-11 Add a new unit for frequencies
2025-09-12 Improve the Makefile
2025-09-18 Add info about the second version of the housing
2025-09-22 Move pictures into a subfolder
2025-09-22 Add a LICENSE file for the pictures
2025-09-22 Add a screenshot of the PCB layout
2025-09-27 Implement LED control throough USB
    Fixes issue #1
2025-09-29 Avoid recompiling if nothing changed
2025-12-07 Use the newly assigned pid.codes product ID
2025-12-15 Implement basic HID boot protocol
    - Only 1-key rollover is supported for now
    - Also fixes code 10 error under Windows
    Fixes issue #4
2025-12-15 Disable LEDs in suspend state
